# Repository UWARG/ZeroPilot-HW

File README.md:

<<<<<<< HEAD
<<<<<<< HEAD
=======

>>>>>>> upstream/master
# WARG-KiCAD

KiCAD libraries to be shared across all WARG projects

### ADDING COMPONENTS

There are 2 steps to add a component. This process is to make it easy to find parts that we previously ordered, and to make it easy to share components across projects.

1)Fill out the component library spreadsheet by adding the new part. Create a new WARG part number using the corresponding prefix. If there isn't a good prefix listed below, add a new 4 letter prefix that reflect the component type.

2) Update the WARG.lib file with the new kicad symbol and store the WARG part number in a new "part_num" field (using the edit field in symbol editor).

### INSTALLING INTO A NEW PROJECT

To add the kiCad library to a new project, add it as a git submodule in your project folder. To do this, use ```git submodule add <url>``` command in the directory you want it added. Also be sure to pull the submodule repo using ```git submodule update --init --recursive```.

Once the submmodule is added, point to your submodule folder using a relative path, and add the WARG.lib to your project libraries.

### GENERATING BOM

To generate a Bill of Materials (BOM), use the generate_warg_bom.py script.

1. In KiCad Eeschema (schematic editor), go to Tools ->Generate Bill of Materials or click on the BOM icon in the toolbar.

2. Click "Add Plugin" and navigate to the generate_warg_bom.py script in \WARG-kicad\bom\generate_warg_bom.py. Click on it. The "Command Line" text field should be auto-completed with something like this:
 ```python "[Your local directory]\WARG\ZeroPilot-HW\WARG-kicad\bom\generate_warg_bom.py" "%I" "%O"  ```

3. Make sure the correct plugin is selected and click "Generate". It will print out the file path of the BOM in csv format

4. Love, cherish, and adore your new bill of materials.

### Component Library Prefixes:

CONN: connector

CHIP: various IC chips

REGU: voltage regulator

RESS: resistor

CAPP: capacitor

INDU: Inductor

DIOD: Diode

XTAL: Cystal

TRAN: Transistor

SENS: Sensor
=======
# ZeroPilot
WARG's future autopilot to replace the PicPilot

# Installation

After cloning the repo, run `git submodule update --init --recursive` to pull in all the submodules.

If you see rendering issues in the schematic or pcb, check to make sure you've got the most updated submodules. To do this, run: `git submodule update --recursive --remote`
>>>>>>> 691a0c99b4d2468f6a5ff89936c726278143d186

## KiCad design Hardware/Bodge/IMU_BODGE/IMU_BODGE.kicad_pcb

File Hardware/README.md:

### ZeroPilot Hardware

#Installing
Install KiCad (http://kicad-pcb.org/) to view and edit the files.

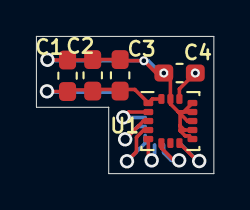
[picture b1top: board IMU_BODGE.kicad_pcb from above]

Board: 2 copper layers, 9.9 x 7.6 mm, 5 parts (0 on the bottom side), 3 nets.

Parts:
C1: 10nF; C_0603_1608Metric_Pad1.05x0.95mm_HandSolder
C2, C4: 100nF; C_0603_1608Metric_Pad1.05x0.95mm_HandSolder
C3: 2.2uF; C_0603_1608Metric_Pad1.05x0.95mm_HandSolder
U1: ICM-20602; LGA-16_3x3mm_P0.5mm_LayoutBorder3x5y

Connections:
/IMU_VDC: C1.1, C2.1, C3.1, U1.1, U1.16
/REGOUT: C4.1, U1.14
GND: C1.2, C2.2, C3.2, C4.2, U1.9, U1.10, U1.11, U1.12, U1.13, U1.15

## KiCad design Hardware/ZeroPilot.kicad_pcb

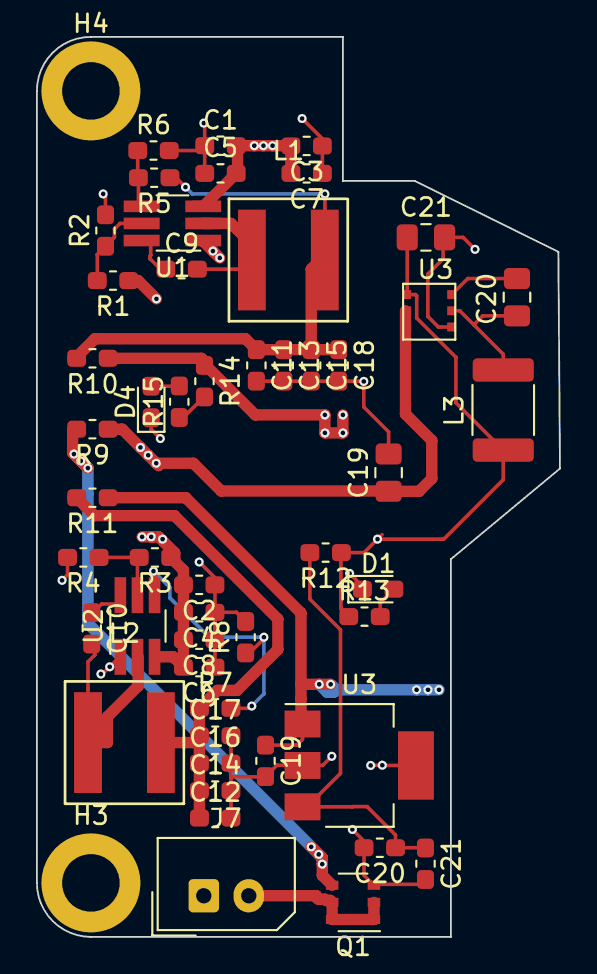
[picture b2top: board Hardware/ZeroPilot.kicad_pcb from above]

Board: 4 copper layers, 29.1 x 50.0 mm, 52 parts (0 on the bottom side), 23 nets.

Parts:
C1, C2: 0.1uF; C_0603_1608Metric_Pad1.05x0.95mm_HandSolder
C3, C4, C5, C6, C7, C8: 6.8uF; C_0603_1608Metric_Pad1.05x0.95mm_HandSolder
C9, C10, C21: 100nF; C_0603_1608Metric_Pad1.05x0.95mm_HandSolder
C11, C12, C13, C14, C15, C16: 22uF; C_0603_1608Metric_Pad1.05x0.95mm_HandSolder
C17, C18, C19, C20: 1uF; C_0603_1608Metric_Pad1.05x0.95mm_HandSolder
C19#2: 10uF; C_0805_2012Metric_Pad1.18x1.45mm_HandSolder
C20#2: 100nF; C_0805_2012Metric_Pad1.18x1.45mm_HandSolder
C21#2: 44uF; C_0805_2012Metric_Pad1.18x1.45mm_HandSolder
D1, D4: PWR_LED; LED_0603_1608Metric_Pad1.05x0.95mm_HandSolder
H3, H4: MountingHole; MountingHole_3.2mm_M3_ISO14580_Pad
J7: SPOX-2; Molex_SPOX_5267-02A_1x02_P2.50mm_Vertical
L1, L2: 15uH; SRP6060FA-150M
L3: 3.9uH; L_1812_4532Metric_Pad1.30x3.40mm_HandSolder
Q1: Q_PMOS_DGS; IRF5806
R1: 210K; R_0603_1608Metric_Pad1.05x0.95mm_HandSolder
R2: 43.2K; R_0603_1608Metric_Pad1.05x0.95mm_HandSolder
R3: 226K; R_0603_1608Metric_Pad1.05x0.95mm_HandSolder
R4: 56K; R_0603_1608Metric_Pad1.05x0.95mm_HandSolder
R5, R7: 100K; R_0603_1608Metric_Pad1.05x0.95mm_HandSolder
R6: 11K; R_0603_1608Metric_Pad1.05x0.95mm_HandSolder
R8: 13.7K; R_0603_1608Metric_Pad1.05x0.95mm_HandSolder
R9, R10, R11, R12: 0; R_0603_1608Metric_Pad1.05x0.95mm_HandSolder
R13, R14, R15: 100; R_0603_1608Metric_Pad1.05x0.95mm_HandSolder
U1: TPS54308; TSOT-23-6_HandSoldering
U2: TPS54308DDCT; TSOT-23-6_HandSoldering
U3: MCP1826S-3302E/DB; SOT-223
U3#2: AP63203WU-7

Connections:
/3V3: C21#2.1, L3.2, R12.1, R13.1, U3#2.1
/5V_INT: C19.1, R11.1, U3.1
/6V_EXT: R10.1, R14.1
/POWER/3V3_JMP: C20.1, C21.1, R12.2, U3.3
/POWER/5V_INT_JMP: C12.1, C14.1, C16.1, C17.1, L2.1, R7.1, R11.2
/POWER/6V_EXT_JMP: C11.1, C13.1, C15.1, C18.1, L1.1, R5.1, R10.2
/POWER/BATT_IN: J7.2, Q1.1
/POWER/EXT_BOOT: C9.1, U1.6
/POWER/EXT_EN: R1.2, R2.1, U1.5
/POWER/EXT_FB: R5.2, R6.1, U1.4
/POWER/EXT_SW: C9.2, L1.2, U1.2
/POWER/INT_BOOT: C10.1, U2.6
/POWER/INT_EN: R3.2, R4.1, U2.5
/POWER/INT_FB: R7.2, R8.1, U2.4
/POWER/INT_SW: C10.2, L2.2, U2.2
/POWER/VBATT_JMP: Q1.3, R9.2
/VBATT: C1.2, C2.2, C3.2, C4.2, C5.2, C6.2, C7.2, C8.2, C19#2.1, R1.1, R3.1, R9.1, U1.3, U2.3, U3#2.2, U3#2.3
GND: C1.1, C2.1, C3.1, C4.1, C5.1, C6.1, C7.1, C8.1, C11.2, C12.2, C13.2, C14.2, C15.2, C16.2, C17.2, C18.2, C19.2, C19#2.2, C20.2, C21.2, C21#2.2, D1.1, D4.1, J7.1, Q1.2, R2.2, R4.2, R6.2, R8.2, U1.1, U2.1, U3.2, U3.4, U3#2.4
unnamed: C20#2.1, U3#2.6
unnamed: C20#2.2, L3.1, U3#2.5
unnamed: D1.2, R13.2
unnamed: D4.2, R15.2
unnamed: R14.2, R15.1

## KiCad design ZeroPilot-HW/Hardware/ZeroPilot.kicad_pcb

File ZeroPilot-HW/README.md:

# ZeroPilot
WARG's future autopilot to replace the PicPilot

# Installation

After cloning the repo, run `git submodule update --init --recursive` to pull in all the submodules.

If you see rendering issues in the schematic or pcb, check to make sure you've got the most updated submodules. To do this, run: `git submodule update --recursive --remote`

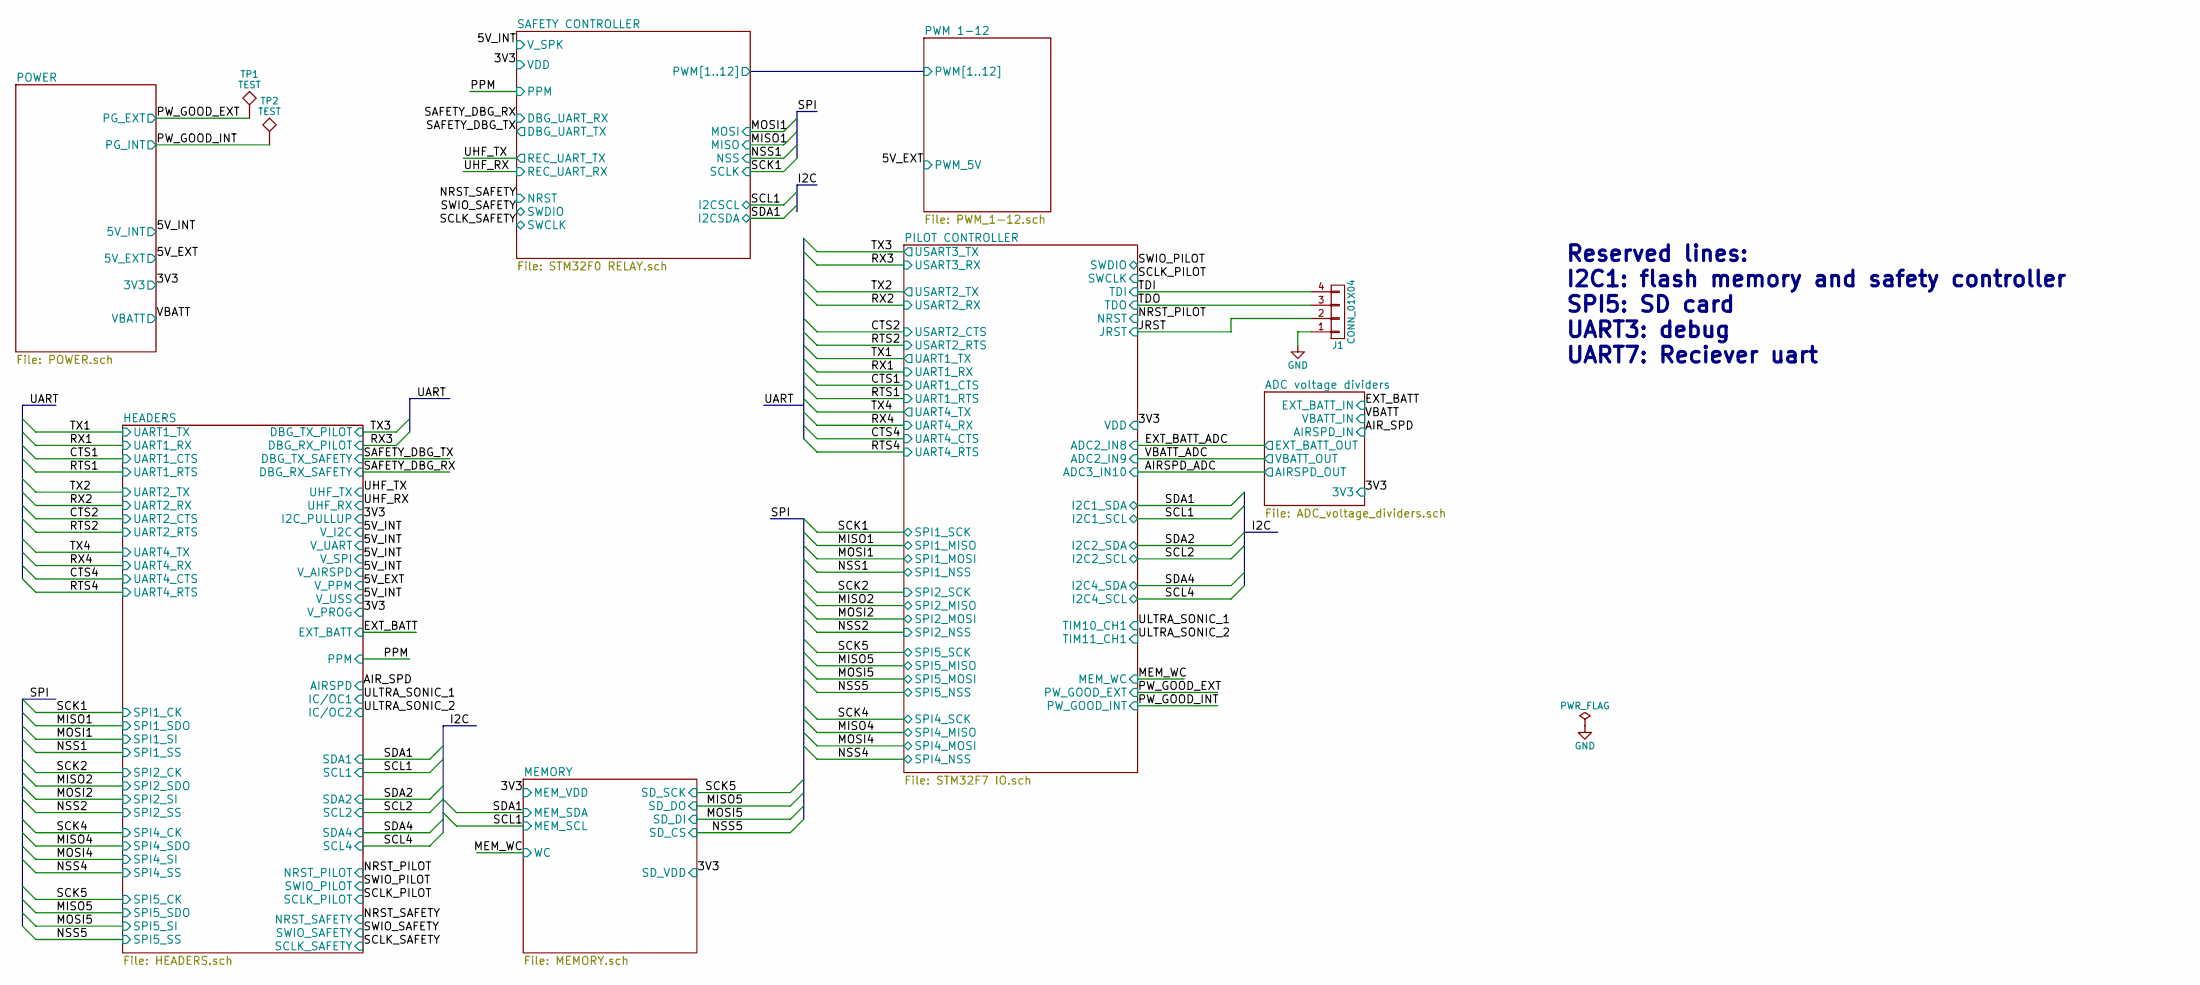
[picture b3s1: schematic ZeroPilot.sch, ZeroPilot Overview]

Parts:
J1: CONN_01X04; Pin_Header_Straight_1x04_Pitch2.54mm; part_num CONN-008
TP1, TP2: TEST; Measurement_Point_Round-SMD-Pad_Small

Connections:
/JRST: J1.2; also elsewhere on the board
/PW_GOOD_EXT: TP1.1; also elsewhere on the board
/PW_GOOD_INT: TP2.1; also elsewhere on the board
/TDI: J1.4; also elsewhere on the board
/TDO: J1.3; also elsewhere on the board
GND: J1.1; also elsewhere on the board

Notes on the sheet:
Reserved lines: I2C1: flash memory and safety controller SPI5: SD card UART3: debug UART7: Reciever uart

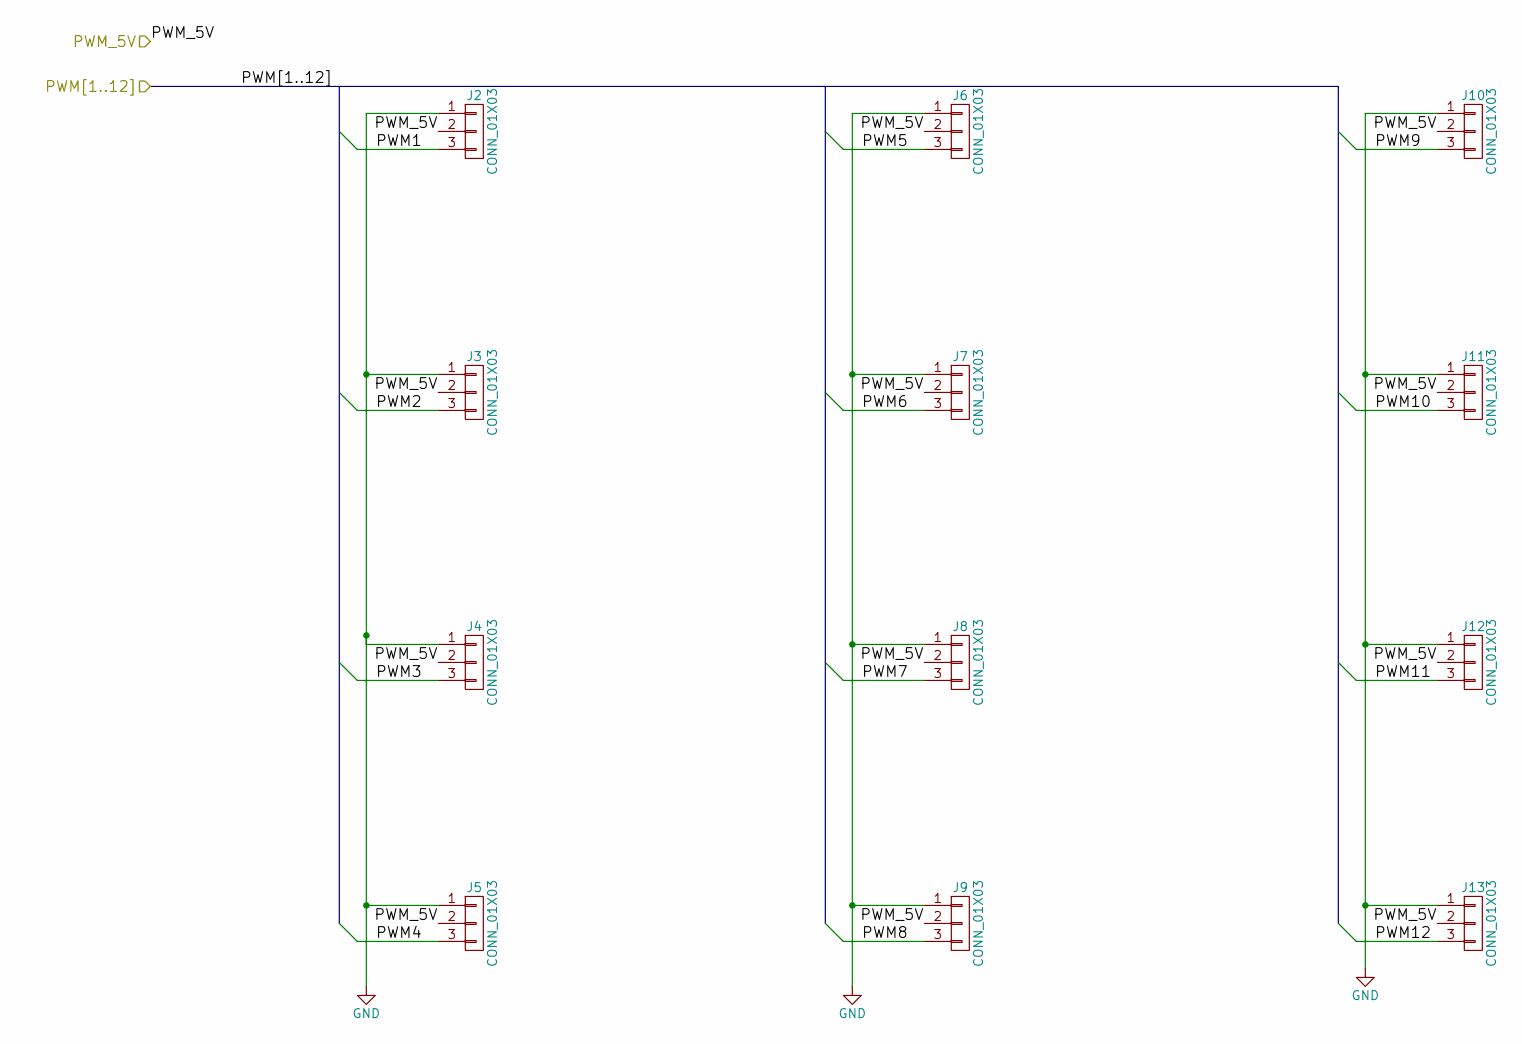
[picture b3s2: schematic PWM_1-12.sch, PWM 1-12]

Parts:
J2, J3, J4, J5, J6, J7, J8, J9, J10, J11, J12, J13: CONN_01X03

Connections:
/5V_EXT: J2.2, J3.2, J4.2, J5.2, J6.2, J7.2, J8.2, J9.2, J10.2, J11.2, J12.2, J13.2; also elsewhere on the board
/PWM 1-12/PWM1: J2.3; also elsewhere on the board
/PWM 1-12/PWM2: J3.3; also elsewhere on the board
/PWM 1-12/PWM3: J4.3; also elsewhere on the board
/PWM 1-12/PWM4: J5.3; also elsewhere on the board
/PWM 1-12/PWM5: J6.3; also elsewhere on the board
/PWM 1-12/PWM6: J7.3; also elsewhere on the board
/PWM 1-12/PWM7: J8.3; also elsewhere on the board
/PWM 1-12/PWM8: J9.3; also elsewhere on the board
/PWM 1-12/PWM9: J10.3; also elsewhere on the board
/PWM 1-12/PWM10: J11.3; also elsewhere on the board
/PWM 1-12/PWM11: J12.3; also elsewhere on the board
/PWM 1-12/PWM12: J13.3; also elsewhere on the board
GND: J2.1, J3.1, J4.1, J5.1, J6.1, J7.1, J8.1, J9.1, J10.1, J11.1, J12.1, J13.1; also elsewhere on the board

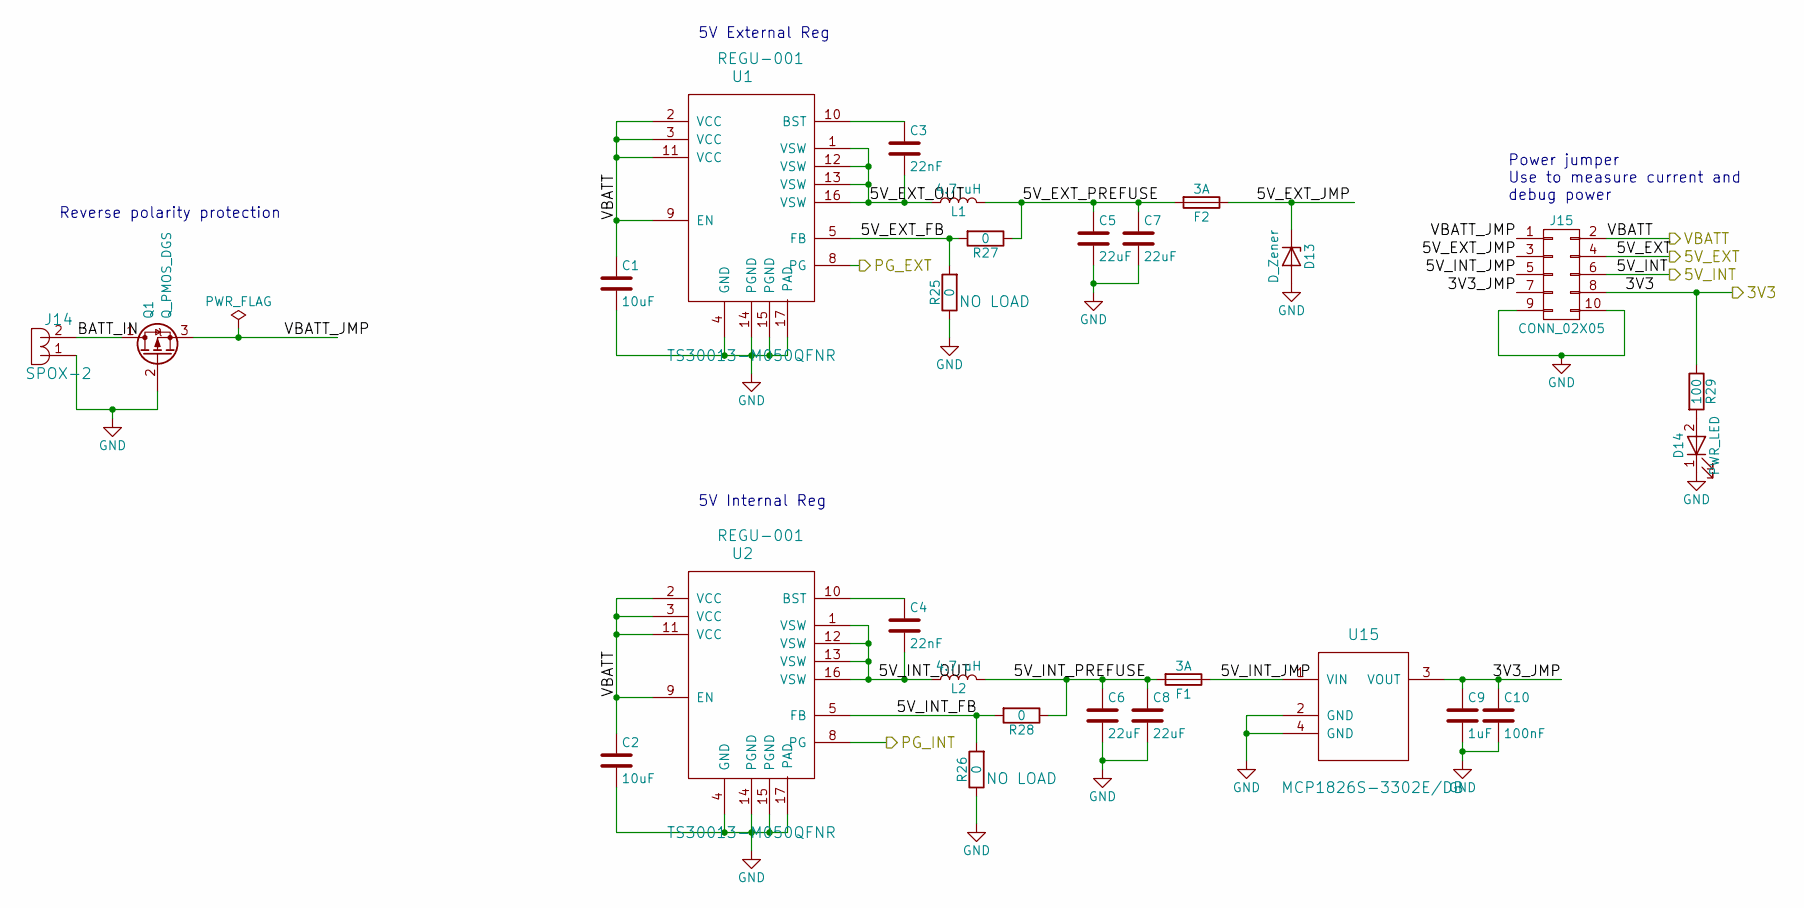
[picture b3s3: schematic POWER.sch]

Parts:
C1, C2: 10uF; R_0603_HandSoldering; part_num CAPP-001
C3, C4: 22nF; R_0603_HandSoldering; part_num CAPP-002
C5, C6, C7, C8: 22uF; R_0603_HandSoldering; part_num CAPP-003
C9: 1uF; R_0603_HandSoldering; part_num CAPP-004
C10: 100nF; R_0603_HandSoldering; part_num CAPP-005
D13: D_Zener; D_SOD-123; part_num DIOD-001
D14: PWR_LED; LED_0603; part_num DIOD-003
F1, F2: 3A; R_0603_HandSoldering; part_num FUSE-001
J14: SPOX-2; Molex_SPOX-5267_22-03-5025_02x2.54mm_Straight; part_num CONN-001
J15: CONN_02X05; Pin_Header_Straight_2x05_Pitch2.54mm; part_num CONN-010
L1, L2: 4.7 uH; 5.1x6.5; part_num INDU-001
Q1: Q_PMOS_DGS; TSOT-23-6_MK06A_HandSoldering; part_num TRAN-001
R25, R26, R27, R28: 0; R_0603_HandSoldering; part_num RESS-001
R29: 100; R_0603_HandSoldering; part_num RESS-006
U1, U2: TS30013-M050QFNR; QFN-16-1EP_3x3mm_Pitch0.5mm; part_num REGU-001
U15: MCP1826S-3302E/DB; SOT-223; part_num REGU-002

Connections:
/3V3: J15.8, R29.1; also elsewhere on the board
/5V_EXT: J15.4; also elsewhere on the board
/5V_INT: J15.6; also elsewhere on the board
/POWER/3V3_JMP: C9.1, C10.1, J15.7, U15.3 (VOUT)
/POWER/5V_EXT_FB: R25.2, R27.2, U1.5 (FB)
/POWER/5V_EXT_JMP: D13.1 (K), F2.1, J15.3
/POWER/5V_EXT_OUT: C3.2, L1.1, U1.1 (VSW), U1.12 (VSW), U1.13 (VSW), U1.16 (VSW)
/POWER/5V_EXT_PREFUSE: C5.1, C7.1, F2.2, L1.2, R27.1
/POWER/5V_INT_FB: R26.2, R28.2, U2.5 (FB)
/POWER/5V_INT_JMP: F1.1, J15.5, U15.1 (VIN)
/POWER/5V_INT_OUT: C4.2, L2.1, U2.1 (VSW), U2.12 (VSW), U2.13 (VSW), U2.16 (VSW)
/POWER/5V_INT_PREFUSE: C6.1, C8.1, F1.2, L2.2, R28.1
/POWER/BATT_IN: J14.2, Q1.1 (D)
/POWER/VBATT_JMP: J15.1, Q1.3 (S)
/PW_GOOD_EXT: U1.8 (PG); also elsewhere on the board
/PW_GOOD_INT: U2.8 (PG); also elsewhere on the board
/VBATT: C1.1, C2.1, J15.2, U1.2 (VCC), U1.3 (VCC), U1.9 (EN), U1.11 (VCC), U2.2 (VCC), U2.3 (VCC), U2.9 (EN), U2.11 (VCC); also elsewhere on the board
GND: C1.2, C2.2, C5.2, C6.2, C7.2, C8.2, C9.2, C10.2, D13.2 (A), D14.1 (K), J14.1, J15.9, J15.10, Q1.2 (G), R25.1, R26.1, U1.4 (GND), U1.14 (PGND), U1.15 (PGND), U1.17 (PAD), U2.4 (GND), U2.14 (PGND), U2.15 (PGND), U2.17 (PAD), U15.2 (GND), U15.4 (GND); also elsewhere on the board
unnamed: C3.1, U1.10 (BST)
unnamed: C4.1, U2.10 (BST)
unnamed: D14.2 (A), R29.2

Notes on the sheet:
5V External Reg
5V Internal Reg
Power jumper Use to measure current and debug power
Reverse polarity protection

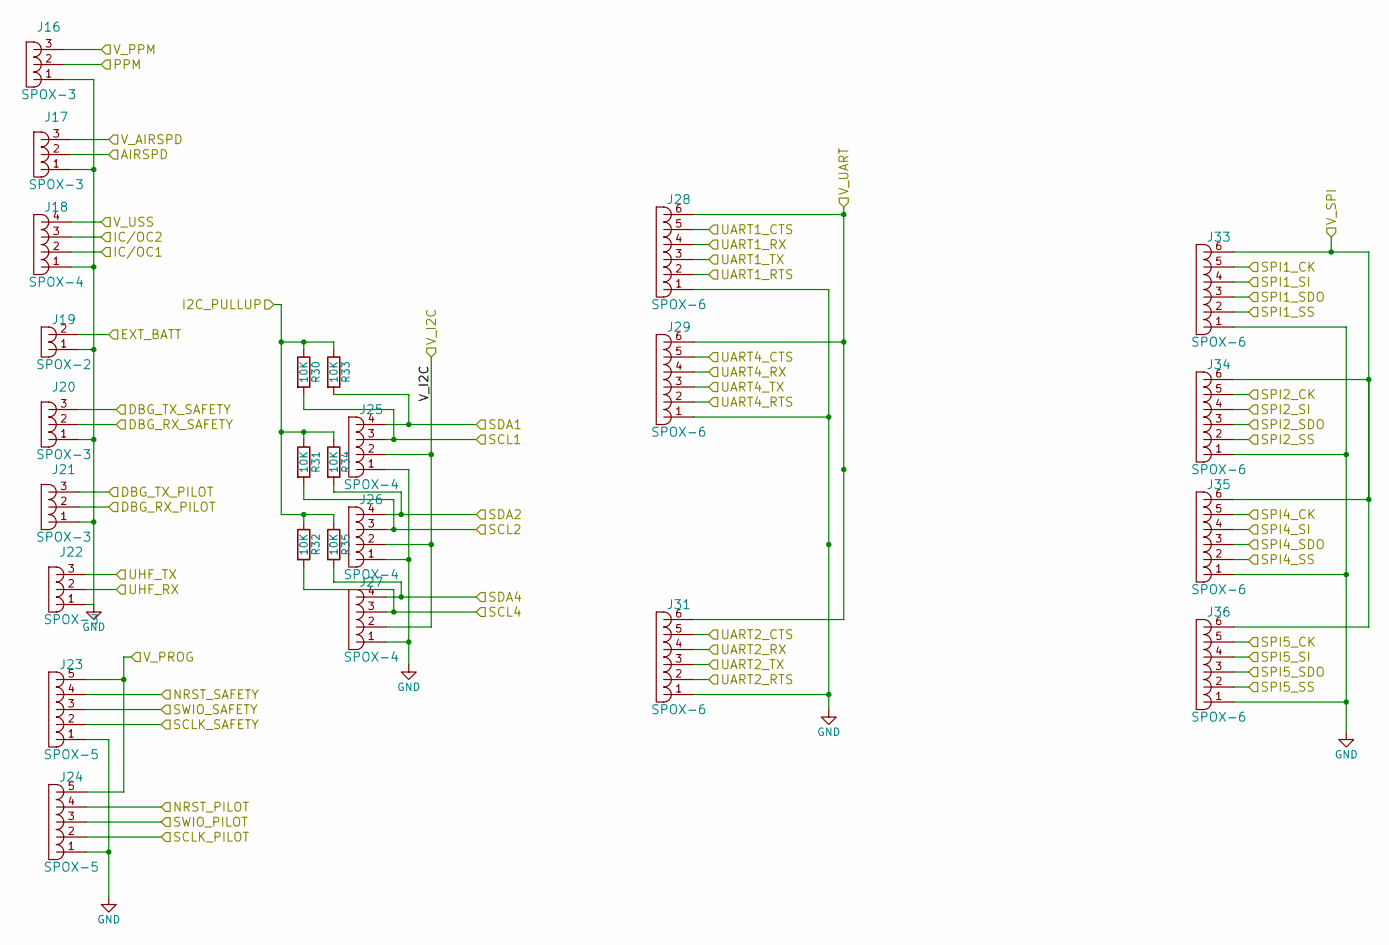
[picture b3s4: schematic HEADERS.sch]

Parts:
J16, J17, J20, J21, J22: SPOX-3; Molex_SPOX-5267_22-03-5035_03x2.54mm_Straight; part_num CONN-002
J18, J25, J26, J27: SPOX-4; Molex_SPOX-5267_22-03-5045_04x2.54mm_Straight; part_num CONN-003
J19: SPOX-2; Molex_SPOX-5267_22-03-5025_02x2.54mm_Straight; part_num CONN-001
J23, J24: SPOX-5; Molex_SPOX-5267_22-03-5055_05x2.54mm_Straight; part_num CONN-004
J28, J29, J31, J33, J34, J35, J36: SPOX-6; Molex_SPOX-5267_22-03-5065_06x2.54mm_Straight; part_num CONN-005
R30, R31, R32, R33, R34, R35: 10K; R_0603_HandSoldering; part_num RESS-005

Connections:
/3V3: J23.5, J24.5, R30.1, R31.1, R32.1, R33.1, R34.1, R35.1; also elsewhere on the board
/5V_EXT: J16.3; also elsewhere on the board
/5V_INT: J17.3, J18.4, J25.2, J26.2, J27.2, J28.6, J29.6, J31.6, J33.6, J34.6, J35.6, J36.6; also elsewhere on the board
/AIR_SPD: J17.2; also elsewhere on the board
/CTS1: J28.5; also elsewhere on the board
/CTS2: J31.5; also elsewhere on the board
/CTS4: J29.5; also elsewhere on the board
/EXT_BATT: J19.2; also elsewhere on the board
/MISO1: J33.3; also elsewhere on the board
/MISO2: J34.3; also elsewhere on the board
/MISO4: J35.3; also elsewhere on the board
/MISO5: J36.3; also elsewhere on the board
/MOSI1: J33.4; also elsewhere on the board
/MOSI2: J34.4; also elsewhere on the board
/MOSI4: J35.4; also elsewhere on the board
/MOSI5: J36.4; also elsewhere on the board
/NRST_PILOT: J24.4; also elsewhere on the board
/NRST_SAFETY: J23.4; also elsewhere on the board
/NSS1: J33.2; also elsewhere on the board
/NSS2: J34.2; also elsewhere on the board
/NSS4: J35.2; also elsewhere on the board
/NSS5: J36.2; also elsewhere on the board
/PPM: J16.2; also elsewhere on the board
/RTS1: J28.2; also elsewhere on the board
/RTS2: J31.2; also elsewhere on the board
/RTS4: J29.2; also elsewhere on the board
/RX1: J28.4; also elsewhere on the board
/RX2: J31.4; also elsewhere on the board
/RX3: J21.2; also elsewhere on the board
/RX4: J29.4; also elsewhere on the board
/SAFETY_DBG_RX: J20.2; also elsewhere on the board
/SAFETY_DBG_TX: J20.3; also elsewhere on the board
/SCK1: J33.5; also elsewhere on the board
/SCK2: J34.5; also elsewhere on the board
/SCK4: J35.5; also elsewhere on the board
/SCK5: J36.5; also elsewhere on the board
/SCL1: J25.3, R30.2; also elsewhere on the board
/SCL2: J26.3, R31.2; also elsewhere on the board
/SCL4: J27.3, R32.2; also elsewhere on the board
/SCLK_PILOT: J24.2; also elsewhere on the board
/SCLK_SAFETY: J23.2; also elsewhere on the board
/SDA1: J25.4, R33.2; also elsewhere on the board
/SDA2: J26.4, R34.2; also elsewhere on the board
/SDA4: J27.4, R35.2; also elsewhere on the board
/SWIO_PILOT: J24.3; also elsewhere on the board
/SWIO_SAFETY: J23.3; also elsewhere on the board
/TX1: J28.3; also elsewhere on the board
/TX2: J31.3; also elsewhere on the board
/TX3: J21.3; also elsewhere on the board
/TX4: J29.3; also elsewhere on the board
/UHF_RX: J22.2; also elsewhere on the board
/UHF_TX: J22.3; also elsewhere on the board
/ULTRA_SONIC_1: J18.2; also elsewhere on the board
/ULTRA_SONIC_2: J18.3; also elsewhere on the board
GND: J16.1, J17.1, J18.1, J19.1, J20.1, J21.1, J22.1, J23.1, J24.1, J25.1, J26.1, J27.1, J28.1, J29.1, J31.1, J33.1, J34.1, J35.1, J36.1; also elsewhere on the board

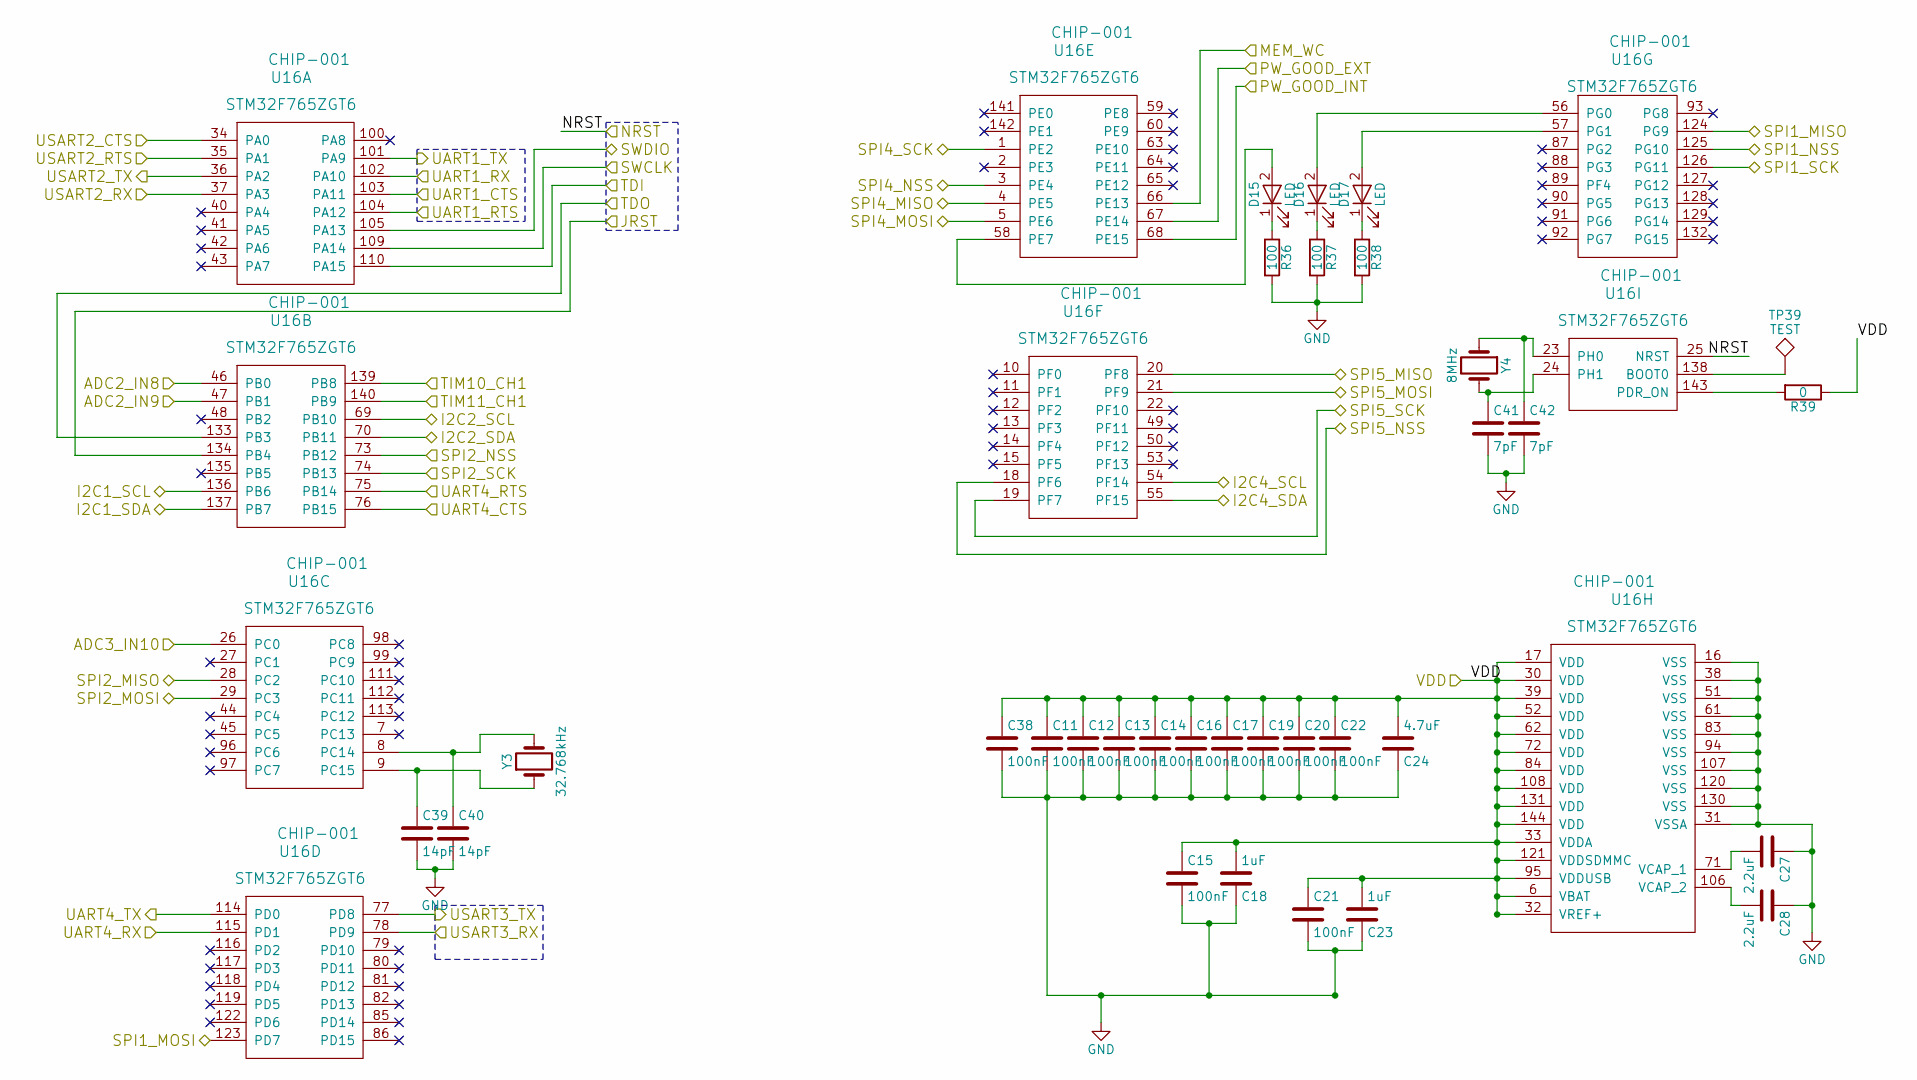
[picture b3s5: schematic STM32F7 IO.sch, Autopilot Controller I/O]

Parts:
C11, C12, C13, C14, C15, C16, C17, C19, C20, C21, C22, C38: 100nF; R_0603_HandSoldering; part_num CAPP-005
C18, C23: 1uF; R_0603_HandSoldering; part_num CAPP-004
C24: 4.7uF; R_0603_HandSoldering; part_num CAPP-006
C27, C28: 2.2uF; R_0603_HandSoldering; part_num CAPP-007
C39, C40: 14pF; R_0603_HandSoldering; part_num CAPP-008
C41, C42: 7pF; R_0603_HandSoldering; part_num CAPP-009
D15, D16, D17: LED; LED_0603; part_num DIOD-002
R36, R37, R38: 100; R_0603_HandSoldering; part_num RESS-006
R39: 0; R_0603_HandSoldering; part_num RESS-001
TP39: TEST; Measurement_Point_Round-SMD-Pad_Small
U16: STM32F765ZGT6; LQFP-144_20x20mm_Pitch0.5mm; part_num CHIP-001
Y3: 32.768kHz; Crystal_SMD_MicroCrystal_CC7V-T1A-2pin_3.2x1.5mm_HandSolder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; part_num XTAL-001
Y4: 8MHz; Crystal_SMD_5032-2pin_5.0x3.2mm_HandSoldering; part_num XTAL-002

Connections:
/3V3: C11.1, C12.1, C13.1, C14.1, C15.1, C16.1, C17.1, C18.2, C19.1, C20.1, C21.1, C22.1, C23.2, C24.2, C38.1, R39.1, U16.6 (VBAT), U16.17 (VDD), U16.30 (VDD), U16.32 (VREF+), U16.33 (VDDA), U16.39 (VDD), U16.52 (VDD), U16.62 (VDD), U16.72 (VDD), U16.84 (VDD), U16.95 (VDDUSB), U16.108 (VDD), U16.121 (VDDSDMMC), U16.131 (VDD), U16.144 (VDD); also elsewhere on the board
/AIRSPD_ADC: U16.26 (PC0); also elsewhere on the board
/CTS1: U16.103 (PA11); also elsewhere on the board
/CTS2: U16.34 (PA0); also elsewhere on the board
/CTS4: U16.76 (PB15); also elsewhere on the board
/EXT_BATT_ADC: U16.46 (PB0); also elsewhere on the board
/JRST: U16.134 (PB4); also elsewhere on the board
/MEM_WC: U16.66 (PE13); also elsewhere on the board
/MISO1: U16.124 (PG9); also elsewhere on the board
/MISO2: U16.28 (PC2); also elsewhere on the board
/MISO4: U16.4 (PE5); also elsewhere on the board
/MISO5: U16.20 (PF8); also elsewhere on the board
/MOSI1: U16.123 (PD7); also elsewhere on the board
/MOSI2: U16.29 (PC3); also elsewhere on the board
/MOSI4: U16.5 (PE6); also elsewhere on the board
/MOSI5: U16.21 (PF9); also elsewhere on the board
/NRST_PILOT: U16.25 (NRST); also elsewhere on the board
/NSS1: U16.125 (PG10); also elsewhere on the board
/NSS2: U16.73 (PB12); also elsewhere on the board
/NSS4: U16.3 (PE4); also elsewhere on the board
/NSS5: U16.18 (PF6); also elsewhere on the board
/PW_GOOD_EXT: U16.67 (PE14); also elsewhere on the board
/PW_GOOD_INT: U16.68 (PE15); also elsewhere on the board
/RTS1: U16.104 (PA12); also elsewhere on the board
/RTS2: U16.35 (PA1); also elsewhere on the board
/RTS4: U16.75 (PB14); also elsewhere on the board
/RX1: U16.102 (PA10); also elsewhere on the board
/RX2: U16.37 (PA3); also elsewhere on the board
/RX3: U16.78 (PD9); also elsewhere on the board
/RX4: U16.115 (PD1); also elsewhere on the board
/SCK1: U16.126 (PG11); also elsewhere on the board
/SCK2: U16.74 (PB13); also elsewhere on the board
/SCK4: U16.1 (PE2); also elsewhere on the board
/SCK5: U16.19 (PF7); also elsewhere on the board
/SCL1: U16.136 (PB6); also elsewhere on the board
/SCL2: U16.69 (PB10); also elsewhere on the board
/SCL4: U16.54 (PF14); also elsewhere on the board
/SCLK_PILOT: U16.109 (PA14); also elsewhere on the board
/SDA1: U16.137 (PB7); also elsewhere on the board
/SDA2: U16.70 (PB11); also elsewhere on the board
/SDA4: U16.55 (PF15); also elsewhere on the board
/SWIO_PILOT: U16.105 (PA13); also elsewhere on the board
/TDI: U16.110 (PA15); also elsewhere on the board
/TDO: U16.133 (PB3); also elsewhere on the board
/TX1: U16.101 (PA9); also elsewhere on the board
/TX2: U16.36 (PA2); also elsewhere on the board
/TX3: U16.77 (PD8); also elsewhere on the board
/TX4: U16.114 (PD0); also elsewhere on the board
/ULTRA_SONIC_1: U16.139 (PB8); also elsewhere on the board
/ULTRA_SONIC_2: U16.140 (PB9); also elsewhere on the board
/VBATT_ADC: U16.47 (PB1); also elsewhere on the board
GND: C11.2, C12.2, C13.2, C14.2, C15.2, C16.2, C17.2, C18.1, C19.2, C20.2, C21.2, C22.2, C23.1, C24.1, C27.1, C28.1, C38.2, C39.2, C40.2, C41.2, C42.2, R36.2, R37.2, R38.2, U16.16 (VSS), U16.31 (VSSA), U16.38 (VSS), U16.51 (VSS), U16.61 (VSS), U16.83 (VSS), U16.94 (VSS), U16.107 (VSS), U16.120 (VSS), U16.130 (VSS); also elsewhere on the board
unnamed: C27.2, U16.71 (VCAP_1)
unnamed: C28.2, U16.106 (VCAP_2)
unnamed: C39.1, U16.9 (PC15), Y3.1
unnamed: C40.1, U16.8 (PC14), Y3.2
unnamed: C41.1, U16.24 (PH1), Y4.2
unnamed: C42.1, U16.23 (PH0), Y4.1
unnamed: D15.1 (K), R36.1
unnamed: D15.2 (A), U16.58 (PE7)
unnamed: D16.1 (K), R37.1
unnamed: D16.2 (A), U16.56 (PG0)
unnamed: D17.1 (K), R38.1
unnamed: D17.2 (A), U16.57 (PG1)
unnamed: R39.2, U16.143 (PDR_ON)
unnamed: TP39.1, U16.138 (BOOT0)

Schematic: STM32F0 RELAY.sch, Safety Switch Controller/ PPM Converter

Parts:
BZ1: Buzzer; AI-1027-TWT-3V-R; part_num BUZZ-001
C29, C30: 14pF; R_0603_HandSoldering; part_num CAPP-008
C31, C32: 7pF; R_0603_HandSoldering; part_num CAPP-009
C33, C34: 100nF; R_0603_HandSoldering; part_num CAPP-005
C35: 4.7uF; R_0603_HandSoldering; part_num CAPP-006
C36: 10nF; R_0603_HandSoldering; part_num CAPP-010
C37: 1uF; R_0603_HandSoldering; part_num CAPP-004
D1, D2, D18: LED; LED_0603; part_num DIOD-002
Q2: Q_NMOS_GSD; TSOT-23; part_num TRAN-002
R1: 100K; R_0603_HandSoldering; part_num RESS-008
R2, R4, R40: 100; R_0603_HandSoldering; part_num RESS-006
TP40: TEST; Measurement_Point_Round-SMD-Pad_Small
U19: STM32F030RCT6; LQFP-64_10x10mm_Pitch0.5mm; part_num CHIP-003
Y1: 32.768kHz; Crystal_SMD_MicroCrystal_CC7V-T1A-2pin_3.2x1.5mm_HandSolder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; part_num XTAL-001
Y2: 8MHz; Crystal_SMD_5032-2pin_5.0x3.2mm_HandSoldering; part_num XTAL-002

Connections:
/3V3: C33.1, C34.1, C35.1, C36.1, C37.1, U19.1, U19.13, U19.19, U19.32, U19.48, U19.64; also elsewhere on the board
/5V_INT: BZ1.1 (-); also elsewhere on the board
/MISO1: U19.56; also elsewhere on the board
/MOSI1: U19.57; also elsewhere on the board
/NRST_SAFETY: U19.7; also elsewhere on the board
/NSS1: U19.50; also elsewhere on the board
/PPM: U19.27; also elsewhere on the board
/PWM 1-12/PWM1: U19.22; also elsewhere on the board
/PWM 1-12/PWM2: U19.23; also elsewhere on the board
/PWM 1-12/PWM3: U19.35; also elsewhere on the board
/PWM 1-12/PWM4: U19.36; also elsewhere on the board
/PWM 1-12/PWM5: U19.37; also elsewhere on the board
/PWM 1-12/PWM6: U19.38; also elsewhere on the board
/PWM 1-12/PWM7: U19.39; also elsewhere on the board
/PWM 1-12/PWM8: U19.40; also elsewhere on the board
/PWM 1-12/PWM9: U19.41; also elsewhere on the board
/PWM 1-12/PWM10: U19.42; also elsewhere on the board
/PWM 1-12/PWM11: U19.43; also elsewhere on the board
/PWM 1-12/PWM12: U19.44; also elsewhere on the board
/SAFETY_DBG_RX: U19.58; also elsewhere on the board
/SAFETY_DBG_TX: U19.59; also elsewhere on the board
/SCK1: U19.55; also elsewhere on the board
/SCL1: U19.61; also elsewhere on the board
/SCLK_SAFETY: U19.49; also elsewhere on the board
/SDA1: U19.62; also elsewhere on the board
/SWIO_SAFETY: U19.46; also elsewhere on the board
/UHF_RX: U19.17; also elsewhere on the board
/UHF_TX: U19.16; also elsewhere on the board
GND: C29.1, C30.1, C31.1, C32.1, C33.2, C34.2, C35.2, C36.2, C37.2, Q2.2, R1.2, R2.2, R4.2, R40.2, U19.12, U19.18, U19.31, U19.47, U19.63; also elsewhere on the board
unnamed: BZ1.2 (+), Q2.3
unnamed: C29.2, U19.3, Y1.1
unnamed: C30.2, U19.4, Y1.2
unnamed: C31.2, U19.5, Y2.1
unnamed: C32.2, U19.6, Y2.2
unnamed: D1.1 (K), R2.1
unnamed: D1.2 (A), U19.53
unnamed: D2.1 (K), R4.1
unnamed: D2.2 (A), U19.51
unnamed: D18.1 (K), R40.1
unnamed: D18.2 (A), U19.52
unnamed: Q2.1, R1.1, U19.34
unnamed: TP40.1, U19.60
